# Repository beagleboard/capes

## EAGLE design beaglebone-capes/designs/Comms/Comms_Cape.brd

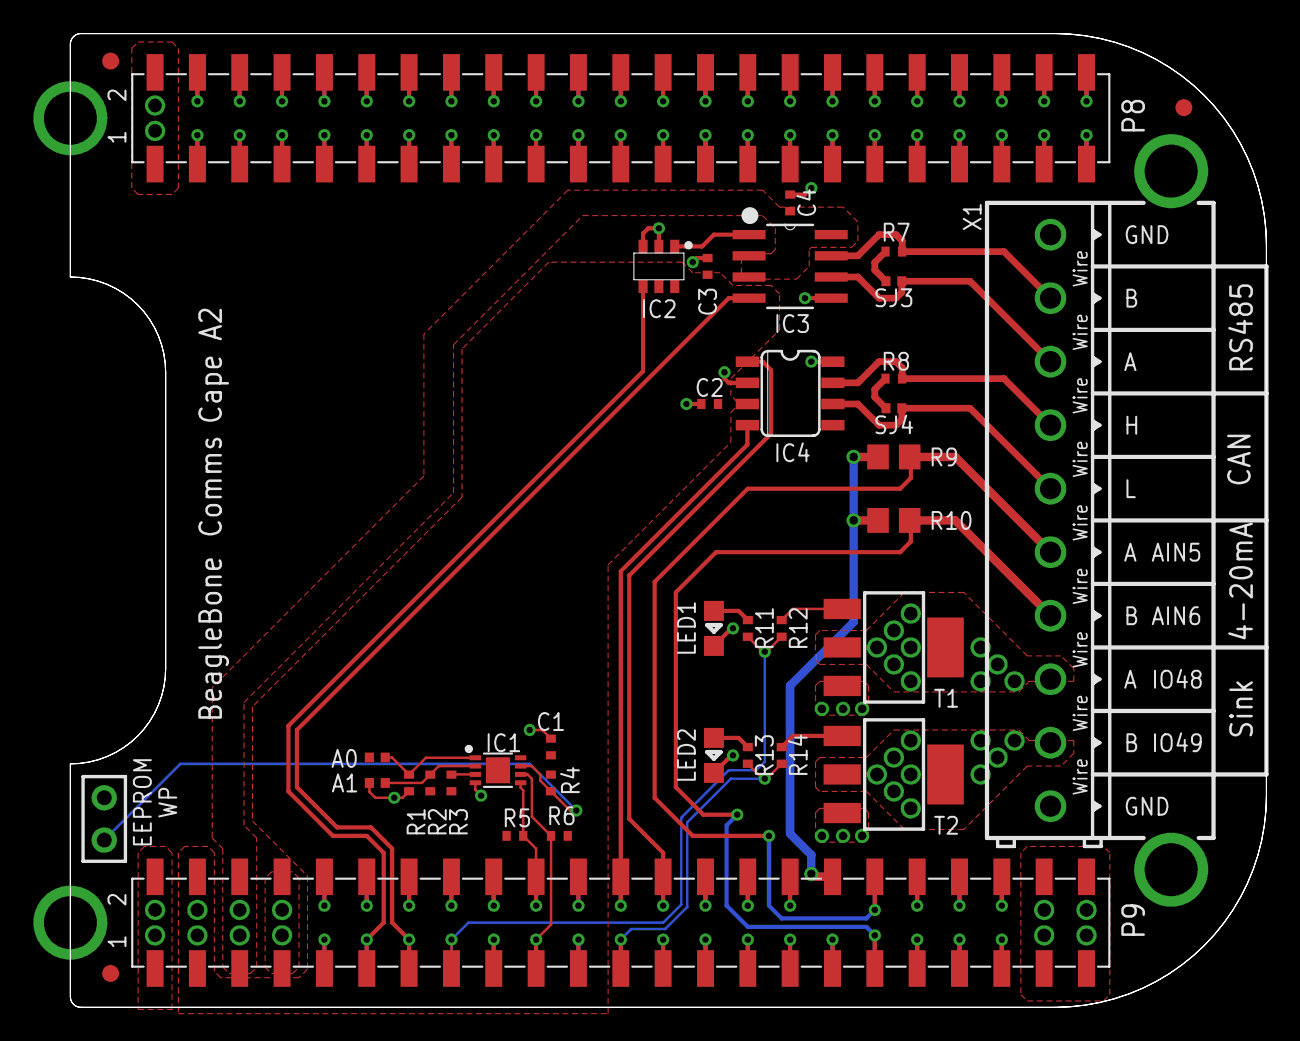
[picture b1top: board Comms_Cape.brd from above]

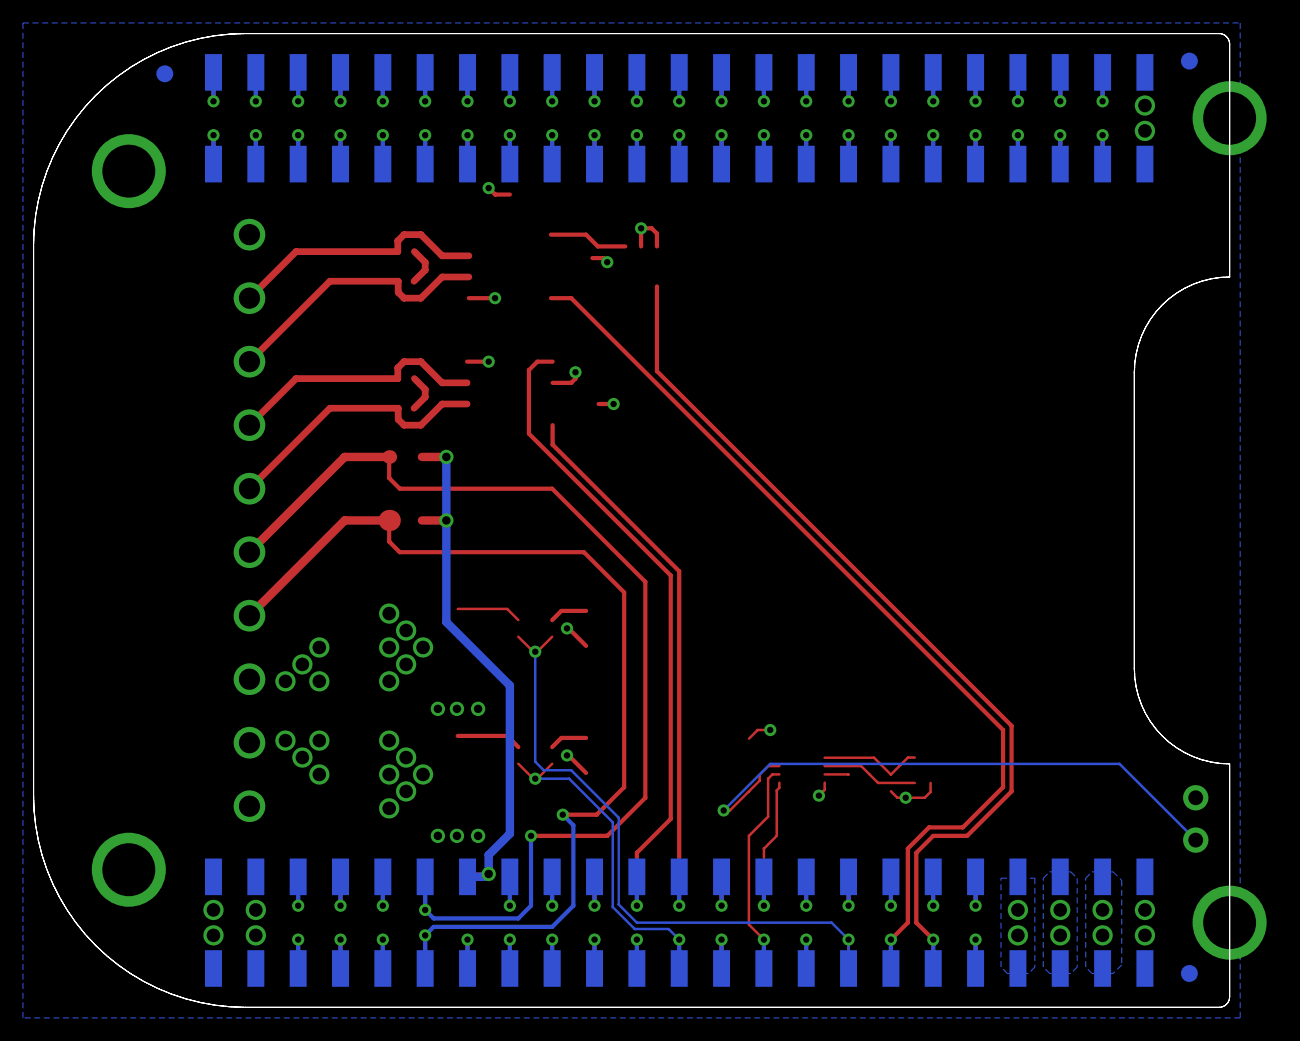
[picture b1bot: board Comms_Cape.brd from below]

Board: 2 copper layers, 71.8 x 58.4 mm, 39 parts (3 on the bottom side), 99 nets.

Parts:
BB.CAPE2: BEAGLEBONE.CAPE.TOP/BOTTOM-PADS
C1, C2, C3, C4: .1uF; 0402
FUD1, FUD2, FUD3, FUD4, FUD5, FUD6: FIDUCIAL; FIDUCIAL_40MIL
IC1: UDFN8,2X3(ON-SEMI)
IC2: 74LVC1G57; SOT-23-6
IC3: MAX13487EESA; SOIC8
IC4: SN65HVD230; SO8
JMP1: JUMPER-(X2)
LED1, LED2: 0805-LED
R1, R2, R3, R4, R11, R13: 1k; 0402
R5, R6: DNP(2.2k); 0402
R7, R8: 120; 0402
R9, R10: 75 .125W; 0805
R12, R14: 330; 0402
SJ1, SJ2, SJ3, SJ4: SOLDER.JOINT(0402)
T1, T2: PBSS4350Z 50V 3A; SOT223
X1: TERMINAL.BLOCK-10TERM-150MIL.PITCH

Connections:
4-20MA.LOOP.A: BB.CAPE2.B9.36, BB.CAPE2.T9.36, R9.2, X1.6
4-20MA.LOOP.B: BB.CAPE2.B9.35, BB.CAPE2.T9.35, R10.2, X1.7
+5V: BB.CAPE2.B9.5, BB.CAPE2.B9.6, BB.CAPE2.T9.5, BB.CAPE2.T9.6, C4.1, IC3.2, IC3.3, IC3.8
A0: IC1.1, R1.2, SJ1.2
A1: IC1.2, R2.2, SJ2.2
A2: IC1.3, R3.2
AGND: BB.CAPE2.B9.34, BB.CAPE2.T9.34, R9.1, R10.1
CAN.H: IC4.7, R8.2, X1.4
CAN.L: IC4.6, SJ4.2, X1.5
CAN.RD: BB.CAPE2.B9.24, BB.CAPE2.T9.24, IC4.4
CAN.TD: BB.CAPE2.B9.26, BB.CAPE2.T9.26, IC4.1
GND: BB.CAPE2.B8.1, BB.CAPE2.B8.2, BB.CAPE2.B9.1, BB.CAPE2.B9.2, BB.CAPE2.B9.43, BB.CAPE2.B9.44, BB.CAPE2.B9.45, BB.CAPE2.B9.46, BB.CAPE2.T8.1, BB.CAPE2.T8.2, BB.CAPE2.T9.1, BB.CAPE2.T9.2, BB.CAPE2.T9.43, BB.CAPE2.T9.44, BB.CAPE2.T9.45, BB.CAPE2.T9.46, C1.2, C2.2, C3.2, C4.2, IC1.4, IC2.GND, IC2.IN0, IC3.5, IC4.2, IC4.8, JMP1.2, LED1.K, LED2.K, R1.1, SJ2.1, T1.3, T2.3, X1.1, X1.10
unnamed: R8.1, SJ4.1
unnamed: R7.1, SJ3.1
unnamed: LED1.A, R11.2
unnamed: LED2.A, R13.2
P8.3: BB.CAPE2.B8.3, BB.CAPE2.T8.3
P8.4: BB.CAPE2.B8.4, BB.CAPE2.T8.4
P8.5: BB.CAPE2.B8.5, BB.CAPE2.T8.5
P8.6: BB.CAPE2.B8.6, BB.CAPE2.T8.6
P8.7: BB.CAPE2.B8.7, BB.CAPE2.T8.7
P8.8: BB.CAPE2.B8.8, BB.CAPE2.T8.8
P8.9: BB.CAPE2.B8.9, BB.CAPE2.T8.9
P8.10: BB.CAPE2.B8.10, BB.CAPE2.T8.10
P8.11: BB.CAPE2.B8.11, BB.CAPE2.T8.11
P8.12: BB.CAPE2.B8.12, BB.CAPE2.T8.12
P8.13: BB.CAPE2.B8.13, BB.CAPE2.T8.13
P8.14: BB.CAPE2.B8.14, BB.CAPE2.T8.14
P8.15: BB.CAPE2.B8.15, BB.CAPE2.T8.15
P8.16: BB.CAPE2.B8.16, BB.CAPE2.T8.16
P8.17: BB.CAPE2.B8.17, BB.CAPE2.T8.17
P8.18: BB.CAPE2.B8.18, BB.CAPE2.T8.18
P8.19: BB.CAPE2.B8.19, BB.CAPE2.T8.19
P8.20: BB.CAPE2.B8.20, BB.CAPE2.T8.20
P8.21: BB.CAPE2.B8.21, BB.CAPE2.T8.21
P8.22: BB.CAPE2.B8.22, BB.CAPE2.T8.22
P8.23: BB.CAPE2.B8.23, BB.CAPE2.T8.23
P8.24: BB.CAPE2.B8.24, BB.CAPE2.T8.24
P8.25: BB.CAPE2.B8.25, BB.CAPE2.T8.25
P8.26: BB.CAPE2.B8.26, BB.CAPE2.T8.26
P8.27: BB.CAPE2.B8.27, BB.CAPE2.T8.27
P8.28: BB.CAPE2.B8.28, BB.CAPE2.T8.28
P8.29: BB.CAPE2.B8.29, BB.CAPE2.T8.29
P8.30: BB.CAPE2.B8.30, BB.CAPE2.T8.30
P8.31: BB.CAPE2.B8.31, BB.CAPE2.T8.31
P8.32: BB.CAPE2.B8.32, BB.CAPE2.T8.32
P8.33: BB.CAPE2.B8.33, BB.CAPE2.T8.33
P8.34: BB.CAPE2.B8.34, BB.CAPE2.T8.34
P8.35: BB.CAPE2.B8.35, BB.CAPE2.T8.35
P8.36: BB.CAPE2.B8.36, BB.CAPE2.T8.36
P8.37: BB.CAPE2.B8.37, BB.CAPE2.T8.37
P8.38: BB.CAPE2.B8.38, BB.CAPE2.T8.38
P8.39: BB.CAPE2.B8.39, BB.CAPE2.T8.39
P8.40: BB.CAPE2.B8.40, BB.CAPE2.T8.40
P8.41: BB.CAPE2.B8.41, BB.CAPE2.T8.41
P8.42: BB.CAPE2.B8.42, BB.CAPE2.T8.42
P8.43: BB.CAPE2.B8.43, BB.CAPE2.T8.43
P8.44: BB.CAPE2.B8.44, BB.CAPE2.T8.44
P8.45: BB.CAPE2.B8.45, BB.CAPE2.T8.45
P8.46: BB.CAPE2.B8.46, BB.CAPE2.T8.46
P9.9: BB.CAPE2.B9.9, BB.CAPE2.T9.9
P9.10: BB.CAPE2.B9.10, BB.CAPE2.T9.10
P9.12: BB.CAPE2.B9.12, BB.CAPE2.T9.12
P9.14: BB.CAPE2.B9.14, BB.CAPE2.T9.14
P9.16: BB.CAPE2.B9.16, BB.CAPE2.T9.16
P9.17: BB.CAPE2.B9.17, BB.CAPE2.T9.17
P9.18: BB.CAPE2.B9.18, BB.CAPE2.T9.18
P9.21: BB.CAPE2.B9.21, BB.CAPE2.T9.21
P9.22: BB.CAPE2.B9.22, BB.CAPE2.T9.22
P9.25: BB.CAPE2.B9.25, BB.CAPE2.T9.25
P9.27: BB.CAPE2.B9.27, BB.CAPE2.T9.27
P9.28: BB.CAPE2.B9.28, BB.CAPE2.T9.28
P9.29: BB.CAPE2.B9.29, BB.CAPE2.T9.29
P9.30: BB.CAPE2.B9.30, BB.CAPE2.T9.30
P9.31: BB.CAPE2.B9.31, BB.CAPE2.T9.31
P9.32: BB.CAPE2.B9.32, BB.CAPE2.T9.32
P9.33: BB.CAPE2.B9.33, BB.CAPE2.T9.33
P9.37: BB.CAPE2.B9.37, BB.CAPE2.T9.37
P9.38: BB.CAPE2.B9.38, BB.CAPE2.T9.38
P9.39: BB.CAPE2.B9.39, BB.CAPE2.T9.39
P9.40: BB.CAPE2.B9.40, BB.CAPE2.T9.40
P9.41: BB.CAPE2.B9.41, BB.CAPE2.T9.41
P9.42: BB.CAPE2.B9.42, BB.CAPE2.T9.42
RS485.A: IC3.6, SJ3.2, X1.3
RS485.B: IC3.7, R7.2, X1.2
RS485.RX: BB.CAPE2.B9.11, BB.CAPE2.T9.11, IC2.Y
RS485.RX.5V: IC2.IN1, IC3.1
RS485.TX: BB.CAPE2.B9.13, BB.CAPE2.T9.13, IC3.4
SCL: BB.CAPE2.B9.19, BB.CAPE2.T9.19, IC1.6, R6.1
SDA: BB.CAPE2.B9.20, BB.CAPE2.T9.20, IC1.5, R5.1
SINK.A: BB.CAPE2.B9.15, BB.CAPE2.T9.15, R11.1, R12.1
SINK.A-BASE: R12.2, T1.1
SINK.A-TB: T1.2, T1.4, X1.8
SINK.B: BB.CAPE2.B9.23, BB.CAPE2.T9.23, R13.1, R14.1
SINK.B-BASE: R14.2, T2.1
SINK.B-TB: T2.2, T2.4, X1.9
SYS.VOUT: BB.CAPE2.B9.7, BB.CAPE2.B9.8, BB.CAPE2.T9.7, BB.CAPE2.T9.8
VCC: BB.CAPE2.B9.3, BB.CAPE2.B9.4, BB.CAPE2.T9.3, BB.CAPE2.T9.4, C1.1, C2.1, C3.1, IC1.8, IC2.IN2, IC2.VCC, IC4.3, R2.1, R3.1, R4.2, R5.2, R6.2, SJ1.1
WP: IC1.7, JMP1.1, R4.1

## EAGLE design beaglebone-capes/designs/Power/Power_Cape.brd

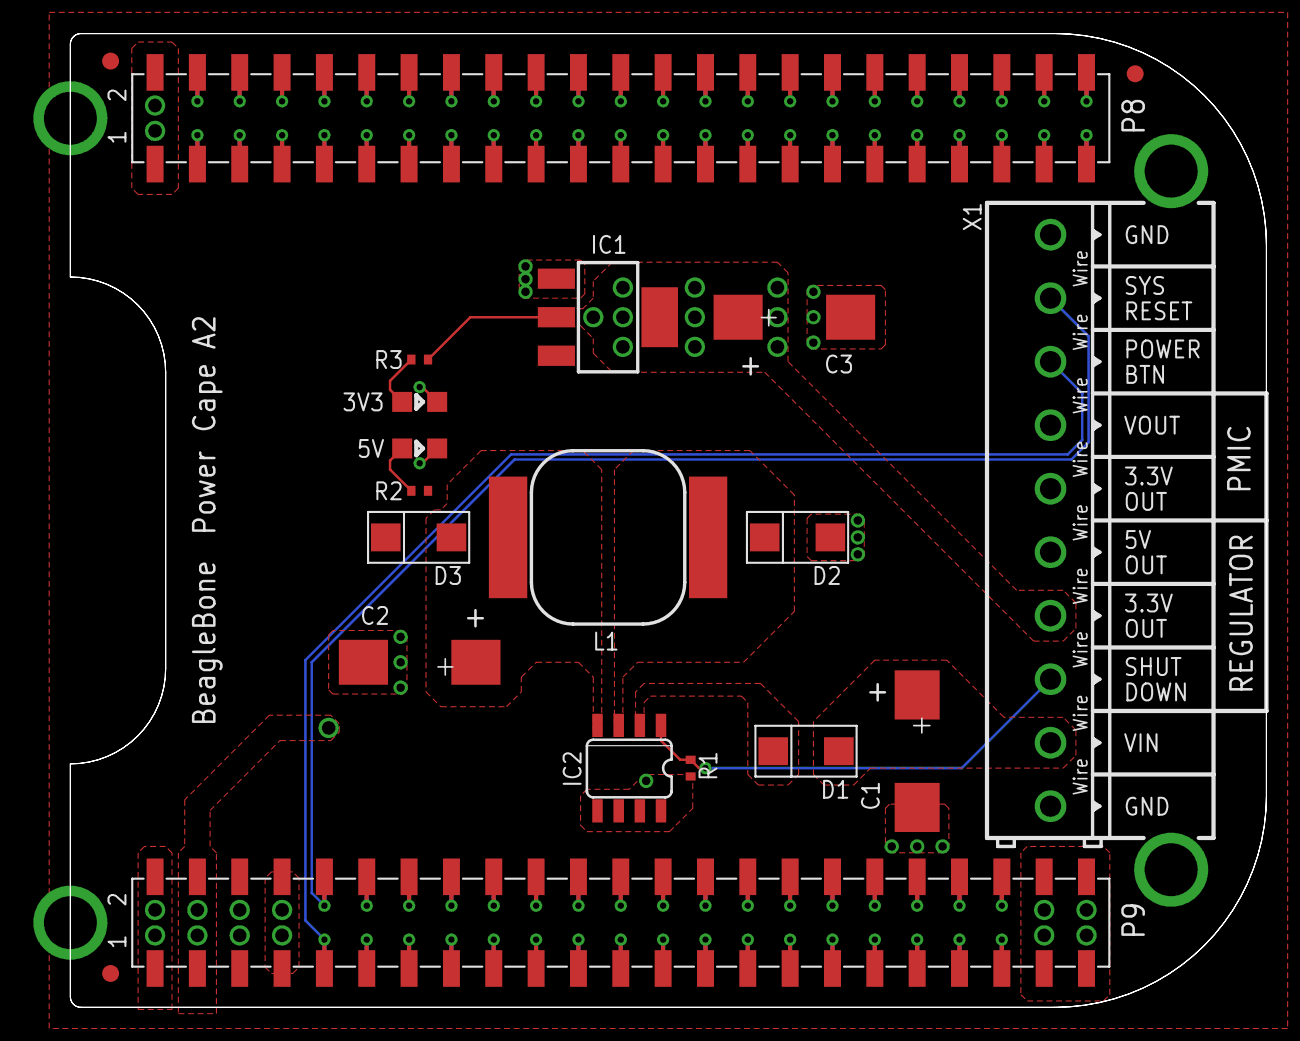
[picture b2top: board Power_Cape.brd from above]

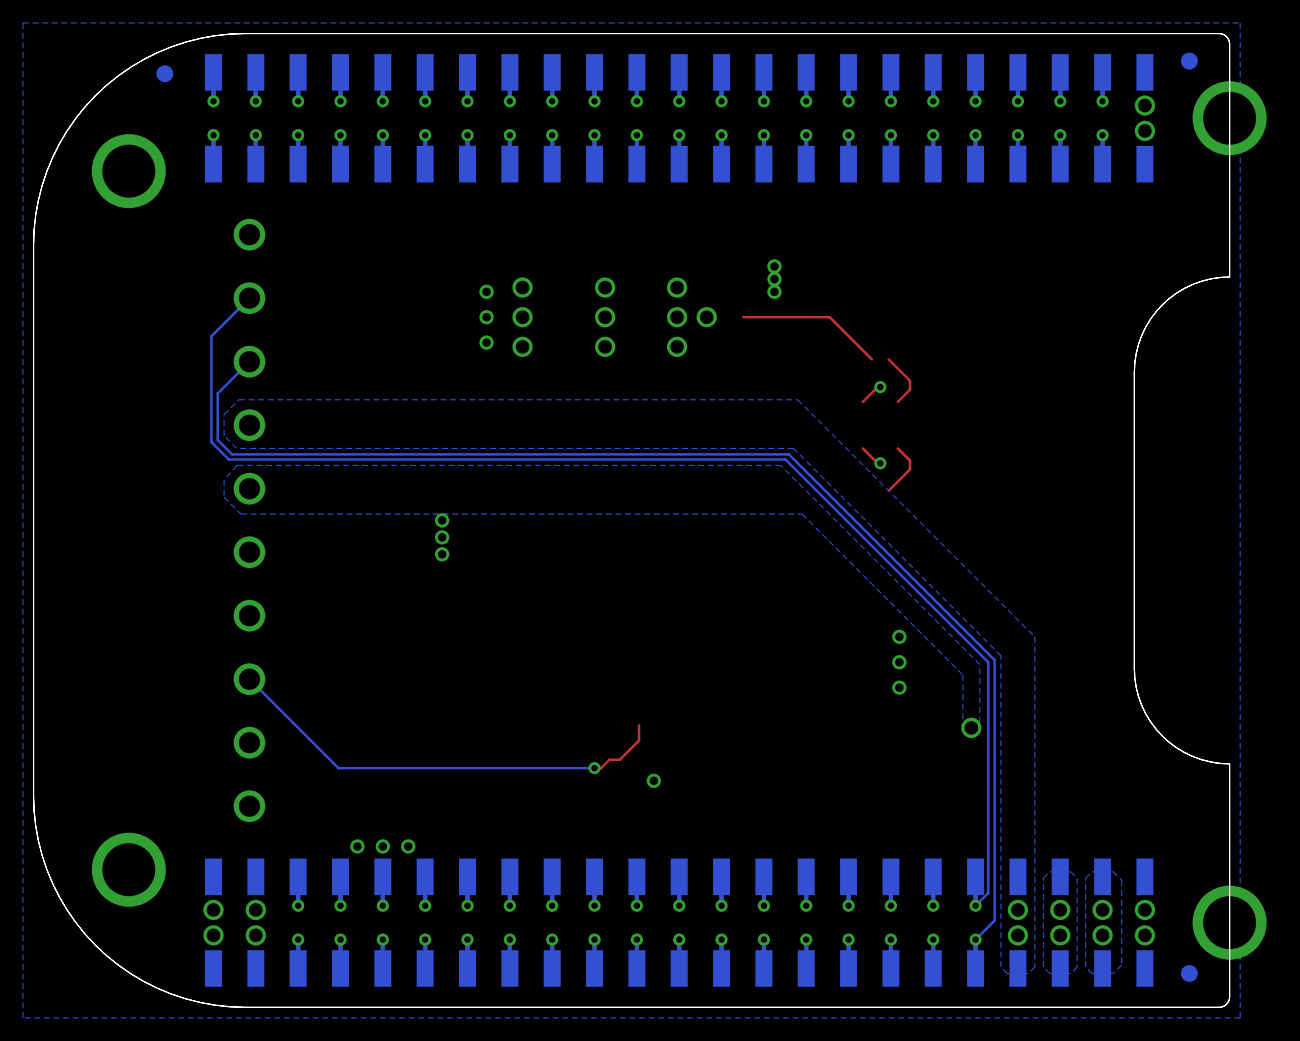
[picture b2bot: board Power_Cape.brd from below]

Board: 2 copper layers, 71.8 x 58.4 mm, 22 parts (3 on the bottom side), 90 nets.

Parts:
3V3, 5V: RED; 0805-LED
BB.CAPE1: BEAGLEBONE.CAPE.TOP/BOTTOM-PADS
C1: 15uF 35V T491D156K035AT; D/7343-31W
C2, C3: 220uF 6.3V B45197A1227K409; D/7343-31W
D1, D3: STPS140A; DIODE_SMA
D2: B130; DIODE_SMA
FUD1, FUD2, FUD3, FUD4, FUD5, FUD6: FIDUCIAL; FIDUCIAL_40MIL
IC1: LM1117MP-3.3; SOT223
IC2: MIC4680-ADJ; SO8
L1: 68uH; UP2B-(UNI-PAC)
R1, R2, R3: 1k; 0402
X1: TERMINAL.BLOCK-10TERM-150MIL.PITCH

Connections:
5VOUT.A: D2.K, IC2.3, L1.1
5VOUT.B: C2.+, D3.A, IC2.4, L1.2
+5V: BB.CAPE1.B9.5, BB.CAPE1.B9.6, BB.CAPE1.T9.5, BB.CAPE1.T9.6, D3.K, IC1.3, R2.1, X1.6
GND: 3V3.K, 5V.K, BB.CAPE1.B8.1, BB.CAPE1.B8.2, BB.CAPE1.B9.1, BB.CAPE1.B9.2, BB.CAPE1.B9.43, BB.CAPE1.B9.44, BB.CAPE1.B9.45, BB.CAPE1.B9.46, BB.CAPE1.T8.1, BB.CAPE1.T8.2, BB.CAPE1.T9.1, BB.CAPE1.T9.2, BB.CAPE1.T9.43, BB.CAPE1.T9.44, BB.CAPE1.T9.45, BB.CAPE1.T9.46, C1.-, C2.-, C3.-, D2.A, IC1.1, IC2.5, IC2.6, IC2.7, IC2.8, R1.2, X1.1, X1.10
unnamed: 5V.A, R2.2
unnamed: 3V3.A, R3.2
P8.3: BB.CAPE1.B8.3, BB.CAPE1.T8.3
P8.4: BB.CAPE1.B8.4, BB.CAPE1.T8.4
P8.5: BB.CAPE1.B8.5, BB.CAPE1.T8.5
P8.6: BB.CAPE1.B8.6, BB.CAPE1.T8.6
P8.7: BB.CAPE1.B8.7, BB.CAPE1.T8.7
P8.8: BB.CAPE1.B8.8, BB.CAPE1.T8.8
P8.9: BB.CAPE1.B8.9, BB.CAPE1.T8.9
P8.10: BB.CAPE1.B8.10, BB.CAPE1.T8.10
P8.11: BB.CAPE1.B8.11, BB.CAPE1.T8.11
P8.12: BB.CAPE1.B8.12, BB.CAPE1.T8.12
P8.13: BB.CAPE1.B8.13, BB.CAPE1.T8.13
P8.14: BB.CAPE1.B8.14, BB.CAPE1.T8.14
P8.15: BB.CAPE1.B8.15, BB.CAPE1.T8.15
P8.16: BB.CAPE1.B8.16, BB.CAPE1.T8.16
P8.17: BB.CAPE1.B8.17, BB.CAPE1.T8.17
P8.18: BB.CAPE1.B8.18, BB.CAPE1.T8.18
P8.19: BB.CAPE1.B8.19, BB.CAPE1.T8.19
P8.20: BB.CAPE1.B8.20, BB.CAPE1.T8.20
P8.21: BB.CAPE1.B8.21, BB.CAPE1.T8.21
P8.22: BB.CAPE1.B8.22, BB.CAPE1.T8.22
P8.23: BB.CAPE1.B8.23, BB.CAPE1.T8.23
P8.24: BB.CAPE1.B8.24, BB.CAPE1.T8.24
P8.25: BB.CAPE1.B8.25, BB.CAPE1.T8.25
P8.26: BB.CAPE1.B8.26, BB.CAPE1.T8.26
P8.27: BB.CAPE1.B8.27, BB.CAPE1.T8.27
P8.28: BB.CAPE1.B8.28, BB.CAPE1.T8.28
P8.29: BB.CAPE1.B8.29, BB.CAPE1.T8.29
P8.30: BB.CAPE1.B8.30, BB.CAPE1.T8.30
P8.31: BB.CAPE1.B8.31, BB.CAPE1.T8.31
P8.32: BB.CAPE1.B8.32, BB.CAPE1.T8.32
P8.33: BB.CAPE1.B8.33, BB.CAPE1.T8.33
P8.34: BB.CAPE1.B8.34, BB.CAPE1.T8.34
P8.35: BB.CAPE1.B8.35, BB.CAPE1.T8.35
P8.36: BB.CAPE1.B8.36, BB.CAPE1.T8.36
P8.37: BB.CAPE1.B8.37, BB.CAPE1.T8.37
P8.38: BB.CAPE1.B8.38, BB.CAPE1.T8.38
P8.39: BB.CAPE1.B8.39, BB.CAPE1.T8.39
P8.40: BB.CAPE1.B8.40, BB.CAPE1.T8.40
P8.41: BB.CAPE1.B8.41, BB.CAPE1.T8.41
P8.42: BB.CAPE1.B8.42, BB.CAPE1.T8.42
P8.43: BB.CAPE1.B8.43, BB.CAPE1.T8.43
P8.44: BB.CAPE1.B8.44, BB.CAPE1.T8.44
P8.45: BB.CAPE1.B8.45, BB.CAPE1.T8.45
P8.46: BB.CAPE1.B8.46, BB.CAPE1.T8.46
P9.11: BB.CAPE1.B9.11, BB.CAPE1.T9.11
P9.12: BB.CAPE1.B9.12, BB.CAPE1.T9.12
P9.13: BB.CAPE1.B9.13, BB.CAPE1.T9.13
P9.14: BB.CAPE1.B9.14, BB.CAPE1.T9.14
P9.15: BB.CAPE1.B9.15, BB.CAPE1.T9.15
P9.16: BB.CAPE1.B9.16, BB.CAPE1.T9.16
P9.17: BB.CAPE1.B9.17, BB.CAPE1.T9.17
P9.18: BB.CAPE1.B9.18, BB.CAPE1.T9.18
P9.19: BB.CAPE1.B9.19, BB.CAPE1.T9.19
P9.20: BB.CAPE1.B9.20, BB.CAPE1.T9.20
P9.21: BB.CAPE1.B9.21, BB.CAPE1.T9.21
P9.22: BB.CAPE1.B9.22, BB.CAPE1.T9.22
P9.23: BB.CAPE1.B9.23, BB.CAPE1.T9.23
P9.24: BB.CAPE1.B9.24, BB.CAPE1.T9.24
P9.25: BB.CAPE1.B9.25, BB.CAPE1.T9.25
P9.26: BB.CAPE1.B9.26, BB.CAPE1.T9.26
P9.27: BB.CAPE1.B9.27, BB.CAPE1.T9.27
P9.28: BB.CAPE1.B9.28, BB.CAPE1.T9.28
P9.29: BB.CAPE1.B9.29, BB.CAPE1.T9.29
P9.30: BB.CAPE1.B9.30, BB.CAPE1.T9.30
P9.31: BB.CAPE1.B9.31, BB.CAPE1.T9.31
P9.32: BB.CAPE1.B9.32, BB.CAPE1.T9.32
P9.33: BB.CAPE1.B9.33, BB.CAPE1.T9.33
P9.34: BB.CAPE1.B9.34, BB.CAPE1.T9.34
P9.35: BB.CAPE1.B9.35, BB.CAPE1.T9.35
P9.36: BB.CAPE1.B9.36, BB.CAPE1.T9.36
P9.37: BB.CAPE1.B9.37, BB.CAPE1.T9.37
P9.38: BB.CAPE1.B9.38, BB.CAPE1.T9.38
P9.39: BB.CAPE1.B9.39, BB.CAPE1.T9.39
P9.40: BB.CAPE1.B9.40, BB.CAPE1.T9.40
P9.41: BB.CAPE1.B9.41, BB.CAPE1.T9.41
P9.42: BB.CAPE1.B9.42, BB.CAPE1.T9.42
PWR.BTN: BB.CAPE1.B9.9, BB.CAPE1.T9.9, X1.3
REG.SHUTDOWN: IC2.1, R1.1, X1.8
REGULATED.3V3: C3.+, IC1.2, IC1.4, R3.1, X1.7
SYS.RESET#: BB.CAPE1.B9.10, BB.CAPE1.T9.10, X1.2
SYS.VOUT: BB.CAPE1.B9.7, BB.CAPE1.B9.8, BB.CAPE1.T9.7, BB.CAPE1.T9.8, X1.4
VCC: BB.CAPE1.B9.3, BB.CAPE1.B9.4, BB.CAPE1.T9.3, BB.CAPE1.T9.4, X1.5
VIN: C1.+, D1.A, X1.9
VIN.K: D1.K, IC2.2

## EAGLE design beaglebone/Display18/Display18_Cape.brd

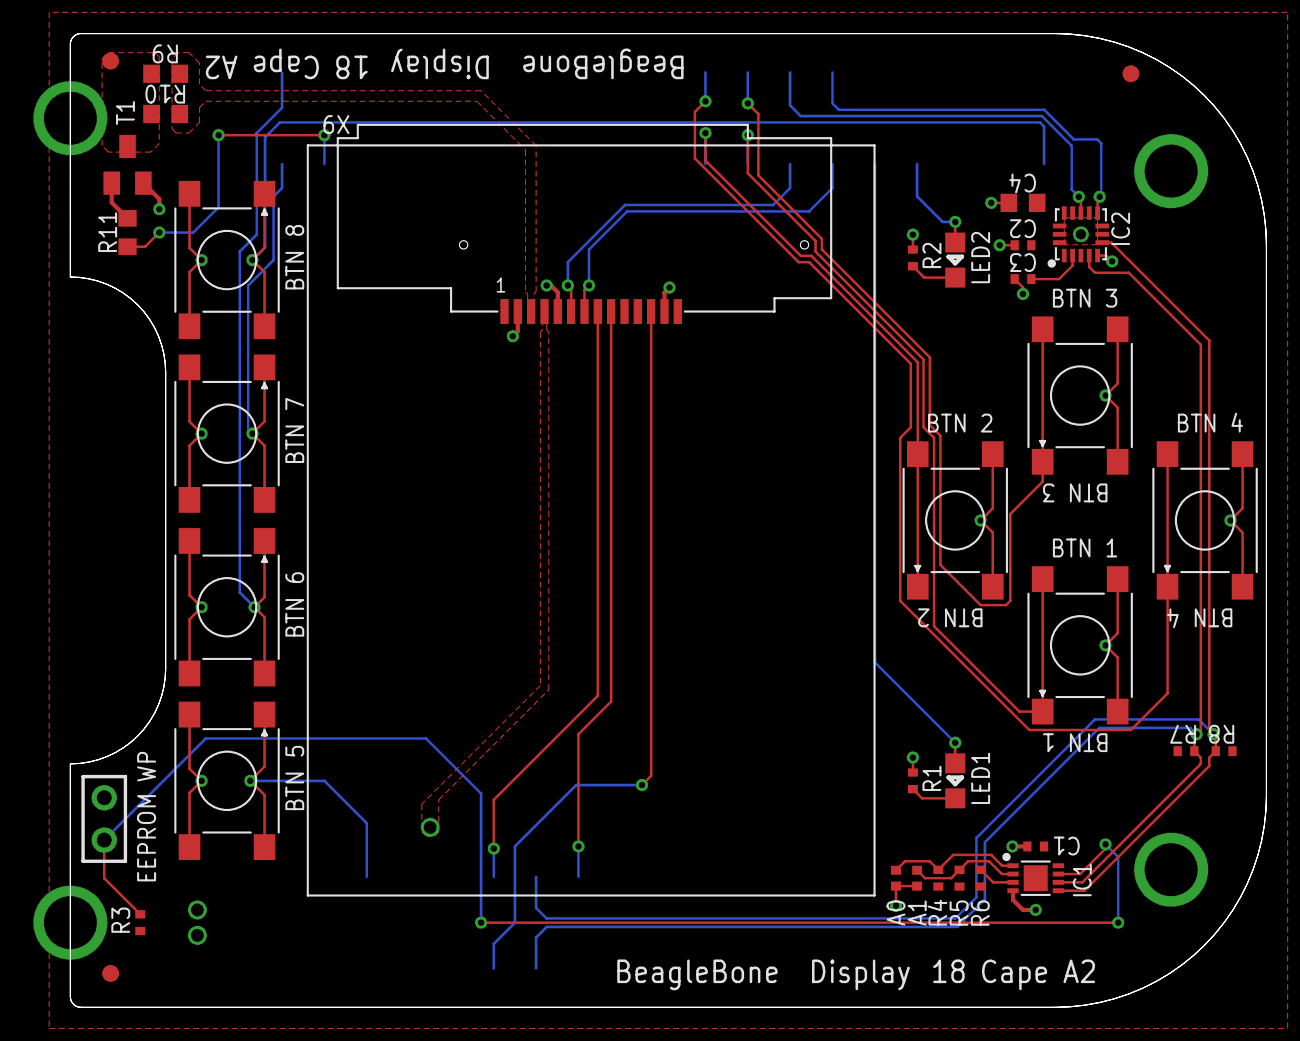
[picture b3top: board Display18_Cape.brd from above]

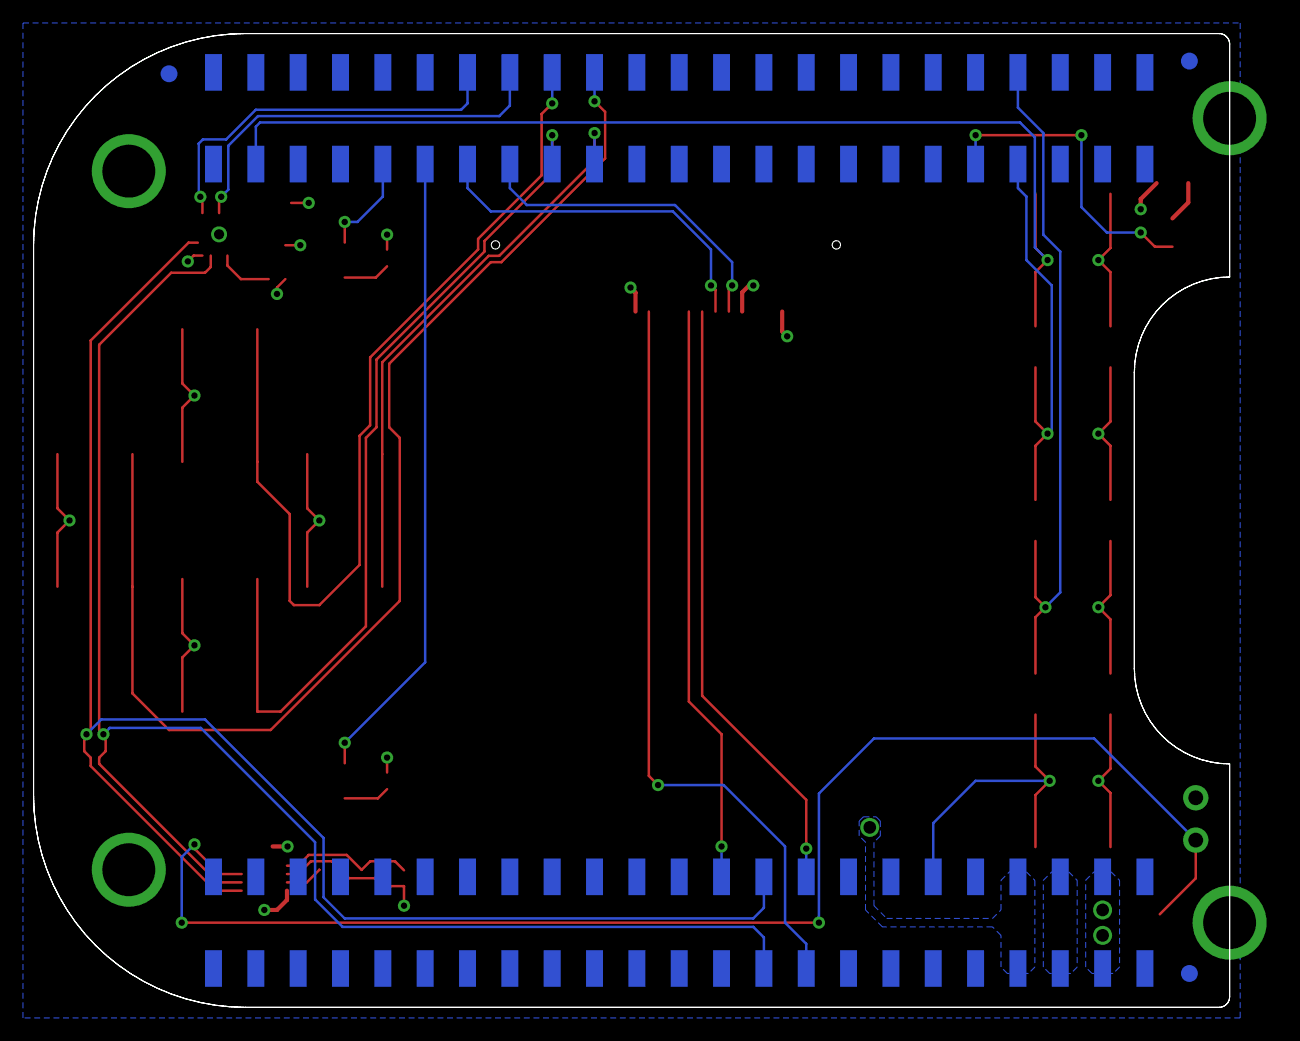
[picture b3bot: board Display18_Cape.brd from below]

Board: 2 copper layers, 71.8 x 58.4 mm, 39 parts (3 on the bottom side), 34 nets.

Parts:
BB.CAPE2: BEAGLEBONE.CAPE.BOTTOM-ONLY-PADS
C1, C2, C3: .1uF; 0402
C4: 4.7uF; 0603
FUD1, FUD2, FUD3, FUD4, FUD5, FUD6: FIDUCIAL; FIDUCIAL_40MIL
IC1: UDFN8,2X3(ON-SEMI)
IC2: QFN-16-(MMA8453Q)
JMP1: JUMPER-(X2)
LED1: GREEN; 0805-LED
LED2: RED; 0805-LED
R1, R2, R3, R4, R5, R6: 1k; 0402
R7, R8: DNP(2.2k); 0402
R9, R10: 120; 0603
R11: 470; 0603
SJ1, SJ2: SOLDER.JOINT(0402)
T1: 3904; SOT23-BEC
X1, X2, X3, X4, X5, X6, X7, X8: 6MM_TACTILE-SWITCH
X9: SPI-LCD-(1.8IN); LCD-(1.8IN)

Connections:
+5V: BB.CAPE2.B9.7, BB.CAPE2.B9.8, X9.4
A0: IC1.1, R4.2, SJ1.2
A1: IC1.2, R5.2, SJ2.2
A2: IC1.3, R6.2
ACC.IRQ1(GPIO11): BB.CAPE2.B8.32, IC2.11
ACC.IRQ2(GPIO81): BB.CAPE2.B8.34, IC2.9
BTN.1(GPIO87): BB.CAPE2.B8.29, X1.1, X1.2
BTN.2(GPIO86): BB.CAPE2.B8.27, X2.1, X2.2
BTN.3(GPIO89): BB.CAPE2.B8.30, X3.1, X3.2
BTN.4(GPIO88): BB.CAPE2.B8.28, X4.1, X4.2
BTN.5(GPIO60): BB.CAPE2.B9.12, X5.1, X5.2
BTN.6(GPIO67): BB.CAPE2.B8.8, X6.1, X6.2
BTN.7(GPIO66): BB.CAPE2.B8.7, X7.1, X7.2
BTN.8(GPIO72): BB.CAPE2.B8.43, X8.1, X8.2
GND: BB.CAPE2.B8.1, BB.CAPE2.B8.2, BB.CAPE2.B9.1, BB.CAPE2.B9.2, BB.CAPE2.B9.43, BB.CAPE2.B9.44, BB.CAPE2.B9.45, BB.CAPE2.B9.46, C1.2, C2.2, C3.2, C4.2, IC1.4, IC2.5, IC2.7, IC2.10, IC2.12, JMP1.2, R1.1, R2.1, SJ1.1, SJ2.1, T1.E, X1.3, X1.4, X2.3, X2.4, X3.3, X3.4, X4.3, X4.4, X5.3, X5.4, X6.3, X6.4, X7.3, X7.4, X8.3, X8.4, X9.2, X9.5, X9.13
LCD.BACKLIGHT(TIMER5): BB.CAPE2.B8.9, R11.2
LCD.DC(GPIO9): BB.CAPE2.B8.33, X9.7
LCD.RESET(GPIO10): BB.CAPE2.B8.31, X9.6
LCD.SPI0.CLK: BB.CAPE2.B9.22, X9.9
LCD.SPI0.CS: BB.CAPE2.B9.17, X9.12
LCD.SPI0.MOSI: BB.CAPE2.B9.18, X9.8
LED1(GPIO8): BB.CAPE2.B8.35, LED1.A
LED2(GPIO78): BB.CAPE2.B8.37, LED2.A
LED.K: R9.1, R10.1, X9.3
unnamed: LED2.K, R2.2
unnamed: LED1.K, R1.2
unnamed: R11.1, T1.B
unnamed: C3.1, IC2.2
SCL: BB.CAPE2.B9.19, IC1.6, IC2.4, R7.1
SDA: BB.CAPE2.B9.20, IC1.5, IC2.6, R8.1
T1.C: R9.2, R10.2, T1.C
VCC: BB.CAPE2.B9.3, BB.CAPE2.B9.4, C1.1, C2.1, C4.1, IC1.8, IC2.1, IC2.14, R3.2, R4.1, R5.1, R6.1, R7.2, R8.2, X9.10, X9.11
VDD_5V: BB.CAPE2.B9.5, BB.CAPE2.B9.6
WP: IC1.7, JMP1.1, R3.1

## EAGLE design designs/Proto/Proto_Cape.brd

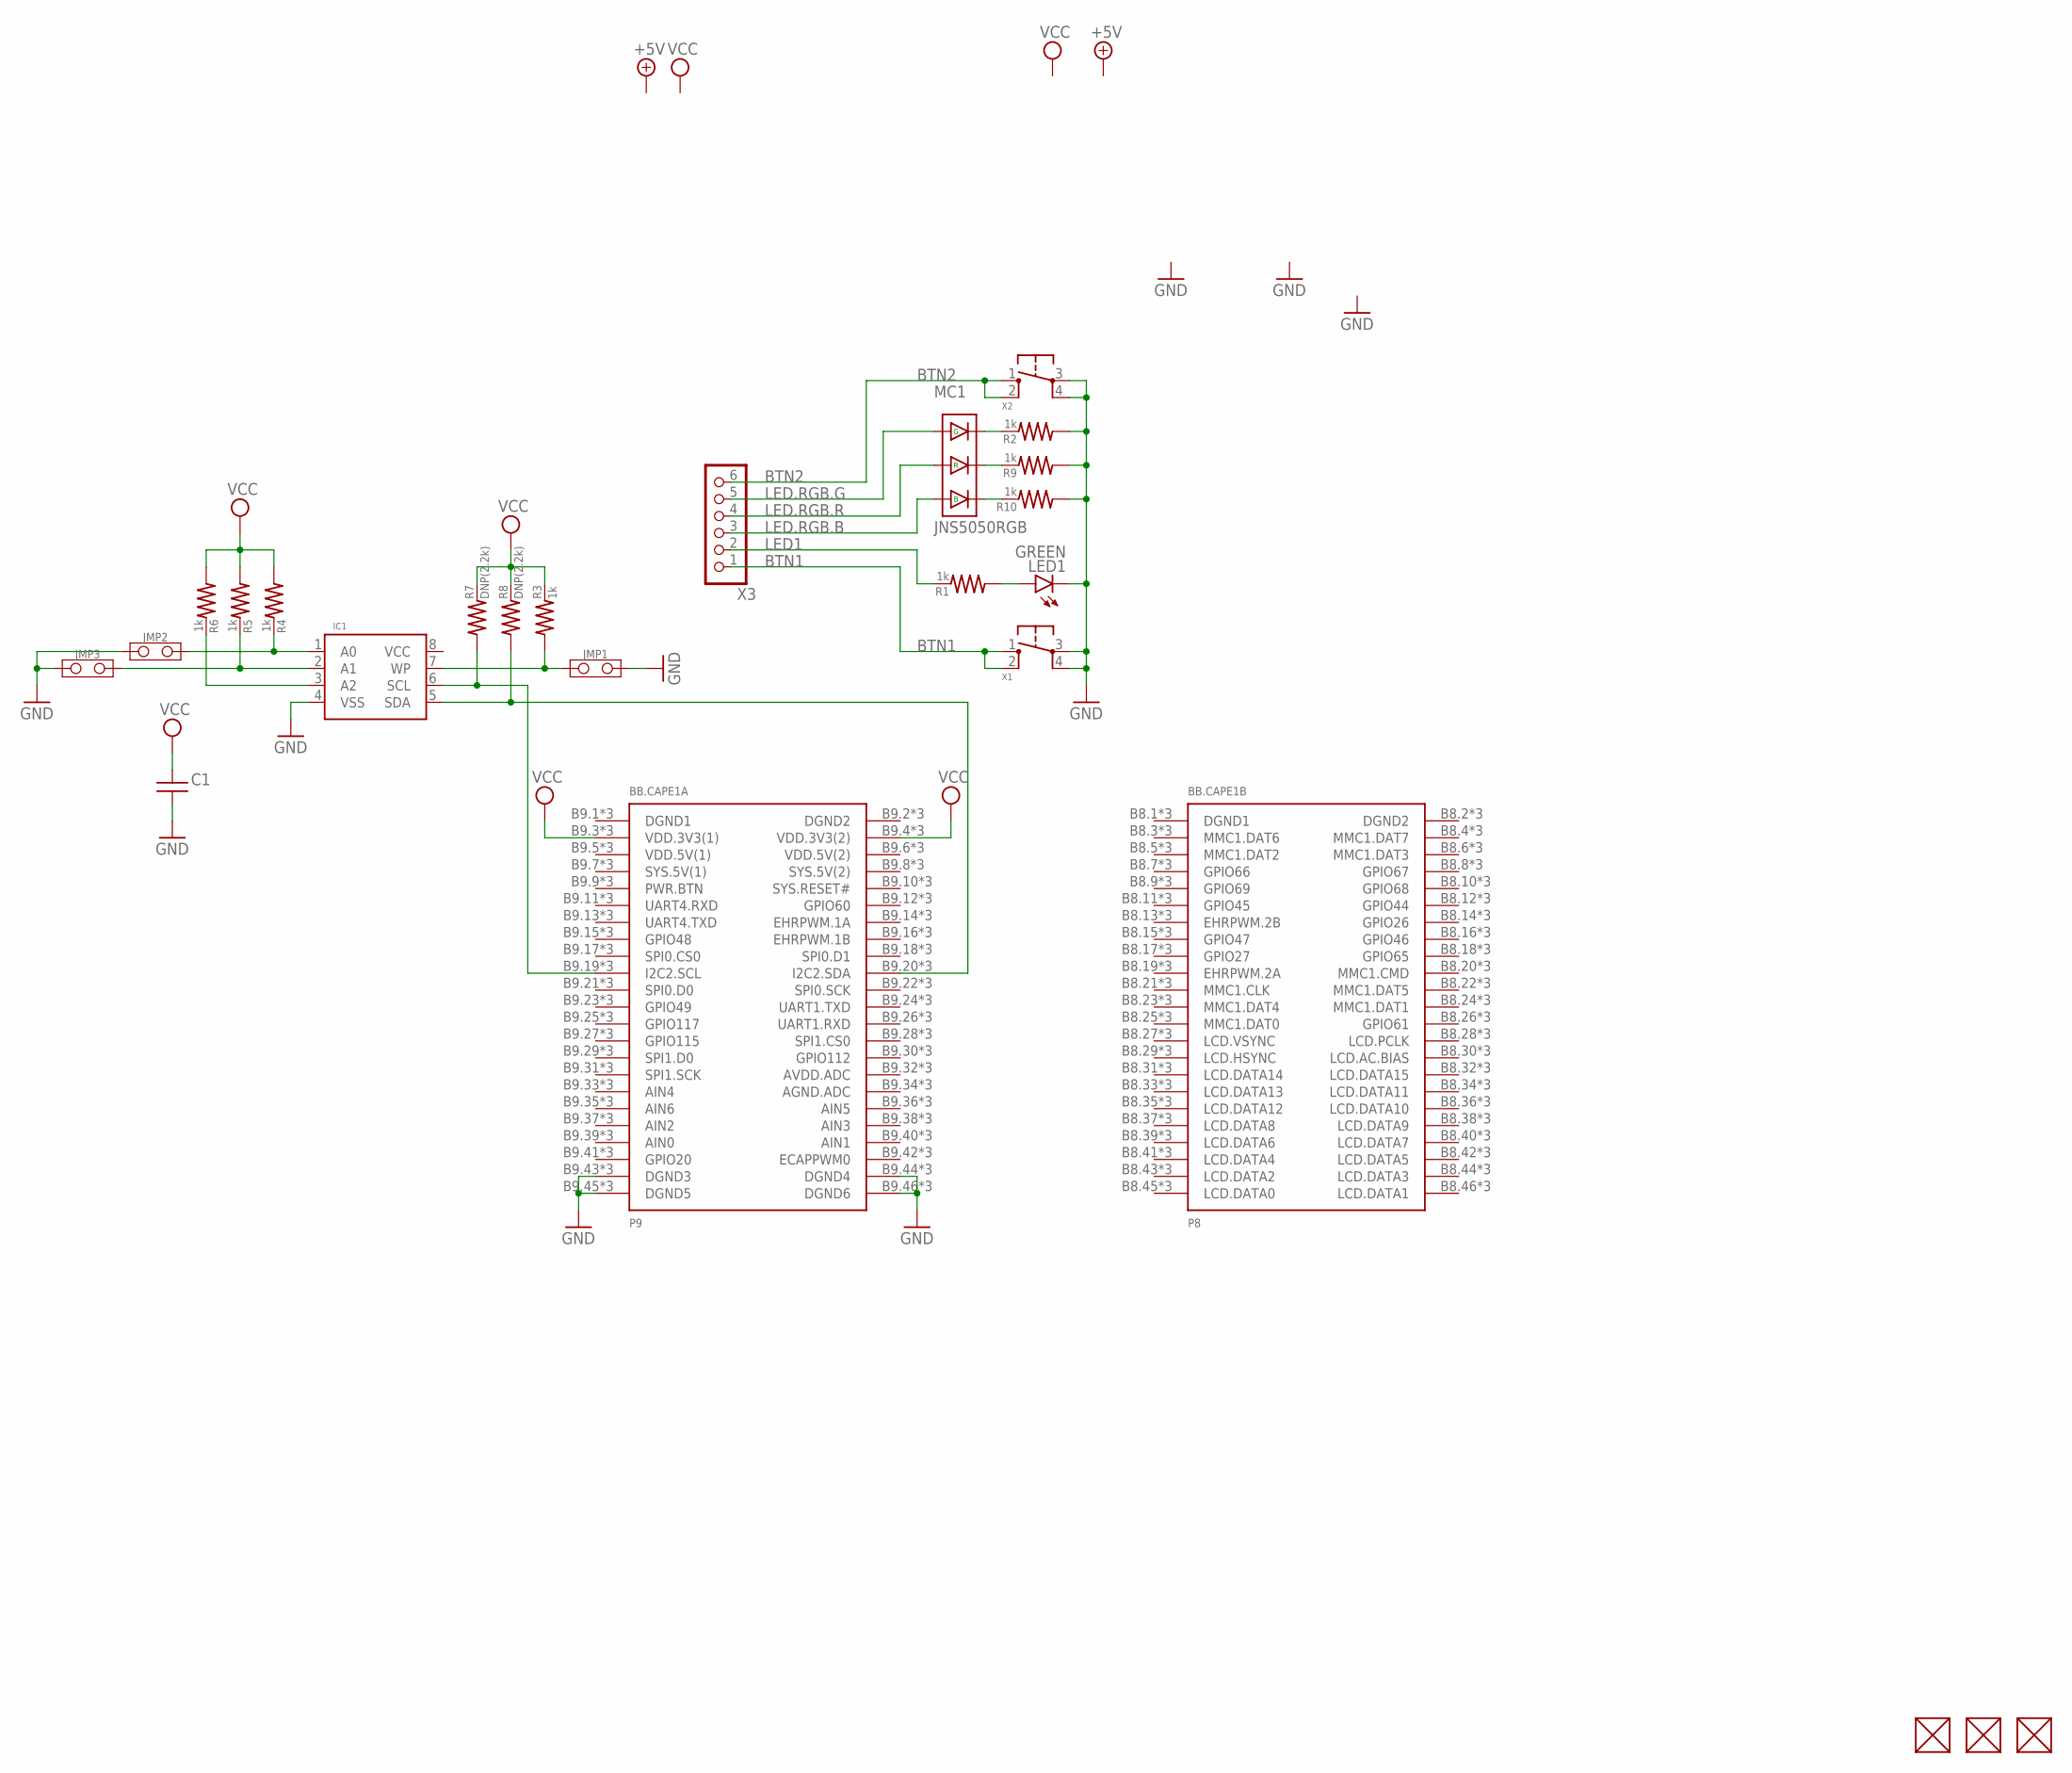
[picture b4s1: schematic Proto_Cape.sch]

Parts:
BB.CAPE1: BEAGLEBONE.CAPE.TOP/BOTTOM-PADS/W/TH; BEAGLEBONE.CAPE.TOP/BOTTOM-PADS.W/TH
C1: CAPACITOR-(INCH)-0402; 0402
FUD1, FUD2, FUD3: FIDUCIAL; FIDUCIAL_40MIL
IC1: CAT24C32; UDFN8,2X3(ON-SEMI)
JMP1, JMP2, JMP3: JUMPER-(X2)
LED1: GREEN; 0805-LED
MC1: JNS5050RGB; LED_RGB_5050
R1, R2, R3, R4, R5, R6, R9, R10: 1k; 0402
R7, R8: DNP(2.2k); 0402
X1, X2: 6MM_TACTILE_SWITCH; 6MM_TACTILE-SWITCH
X3: 1X6-(INCH)-0.1-SMT; SMT-1X6

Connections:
A0: IC1.1 (A0), JMP2.2, R4.2
A1: IC1.2 (A1), JMP3.2, R5.2
A2: IC1.3 (A2), R6.2
BTN1: X1.1, X1.2, X3.1
BTN2: X2.1, X2.2, X3.6
GND: BB.CAPE1.B9.43 (DGND3), BB.CAPE1.B9.44 (DGND4), BB.CAPE1.B9.45 (DGND5), BB.CAPE1.B9.46 (DGND6), BB.CAPE1.P9.43 (DGND3), BB.CAPE1.P9.44 (DGND4), BB.CAPE1.P9.45 (DGND5), BB.CAPE1.P9.46 (DGND6), BB.CAPE1.T9.43 (DGND3), BB.CAPE1.T9.44 (DGND4), BB.CAPE1.T9.45 (DGND5), BB.CAPE1.T9.46 (DGND6), C1.2, IC1.4 (VSS), JMP1.2, JMP2.1, JMP3.1, LED1.K, R2.1, R9.1, R10.1, X1.3, X1.4, X2.3, X2.4
LED1: R1.2, X3.2
LED.RGB.B: MC1.1(+), X3.3
LED.RGB.G: MC1.3(+), X3.5
LED.RGB.R: MC1.2(+), X3.4
unnamed: MC1.4(-), R2.2
unnamed: MC1.5(-), R9.2
unnamed: MC1.6(-), R10.2
unnamed: LED1.A, R1.1
SCL: BB.CAPE1.B9.19 (I2C2.SCL), BB.CAPE1.P9.19 (I2C2.SCL), BB.CAPE1.T9.19 (I2C2.SCL), IC1.6 (SCL), R7.1
SDA: BB.CAPE1.B9.20 (I2C2.SDA), BB.CAPE1.P9.20 (I2C2.SDA), BB.CAPE1.T9.20 (I2C2.SDA), IC1.5 (SDA), R8.1
VCC: BB.CAPE1.B9.3 (VDD.3V3(1)), BB.CAPE1.B9.4 (VDD.3V3(2)), BB.CAPE1.P9.3 (VDD.3V3(1)), BB.CAPE1.P9.4 (VDD.3V3(2)), BB.CAPE1.T9.3 (VDD.3V3(1)), BB.CAPE1.T9.4 (VDD.3V3(2)), C1.1, R3.2, R4.1, R5.1, R6.1, R7.2, R8.2
WP: IC1.7 (WP), JMP1.1, R3.1

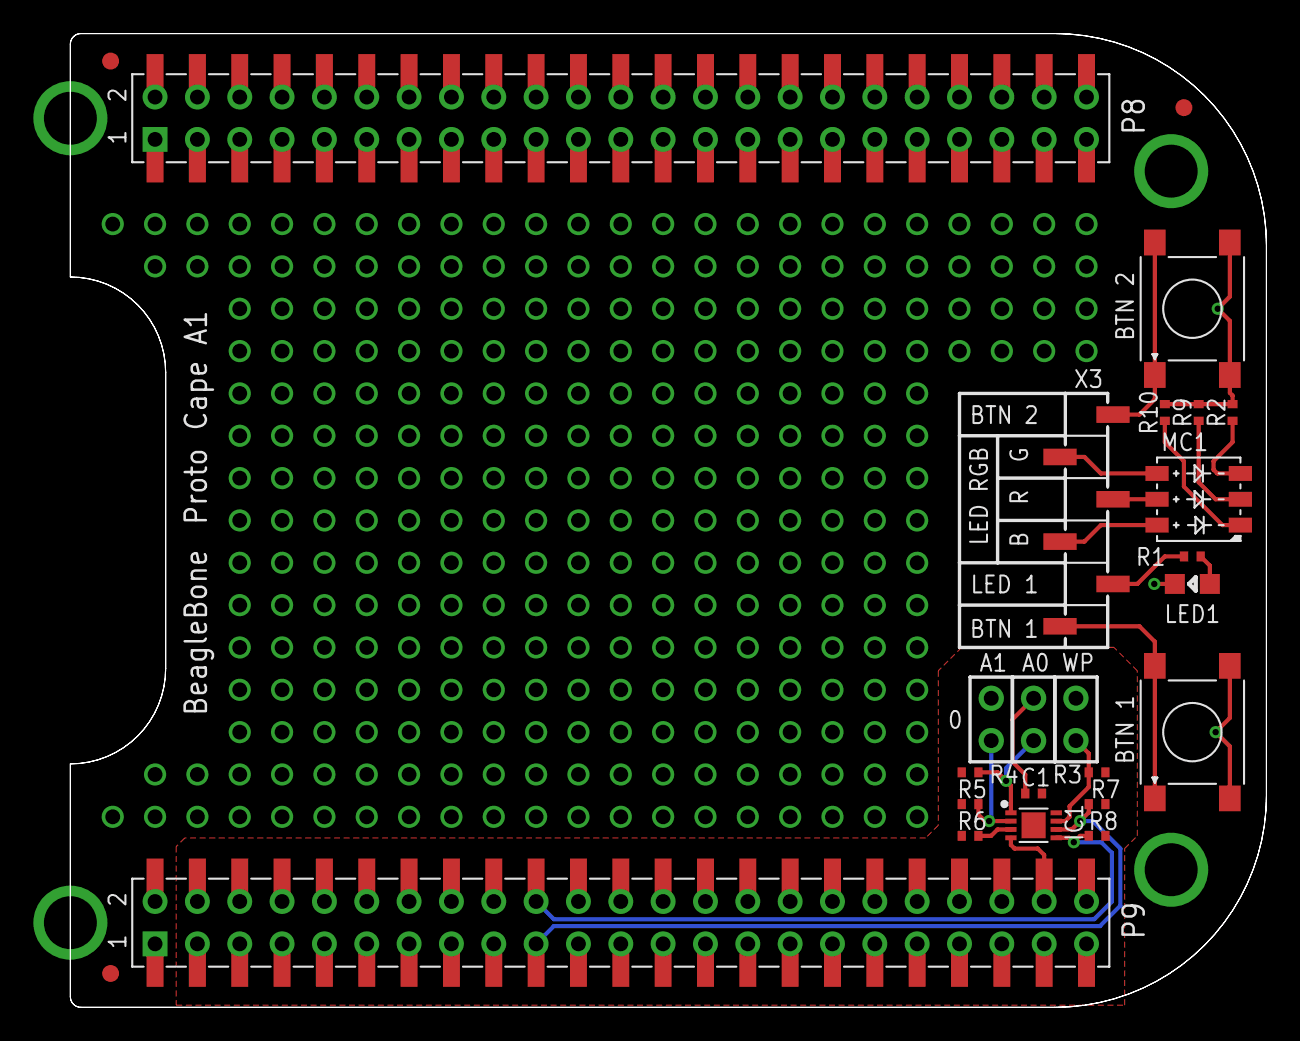
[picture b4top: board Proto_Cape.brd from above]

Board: 2 copper layers, 71.8 x 58.4 mm, 24 parts (0 on the bottom side), 18 nets.

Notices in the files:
parts and their libraries:
SparkFun-Aesthetics: Licensing: CC v3.0 Share-Alike You are welcome to use this library for commercial purposes.
